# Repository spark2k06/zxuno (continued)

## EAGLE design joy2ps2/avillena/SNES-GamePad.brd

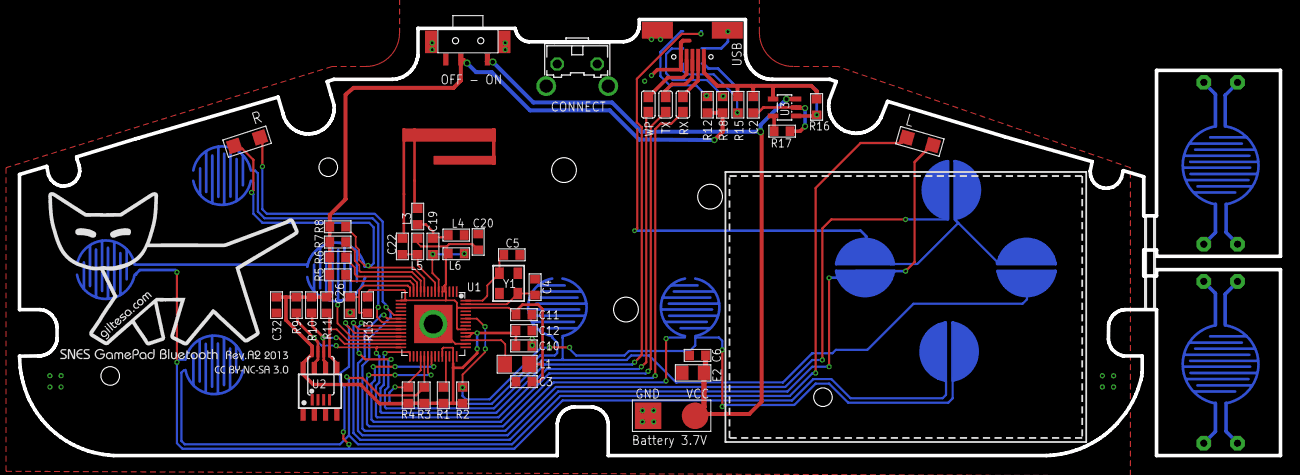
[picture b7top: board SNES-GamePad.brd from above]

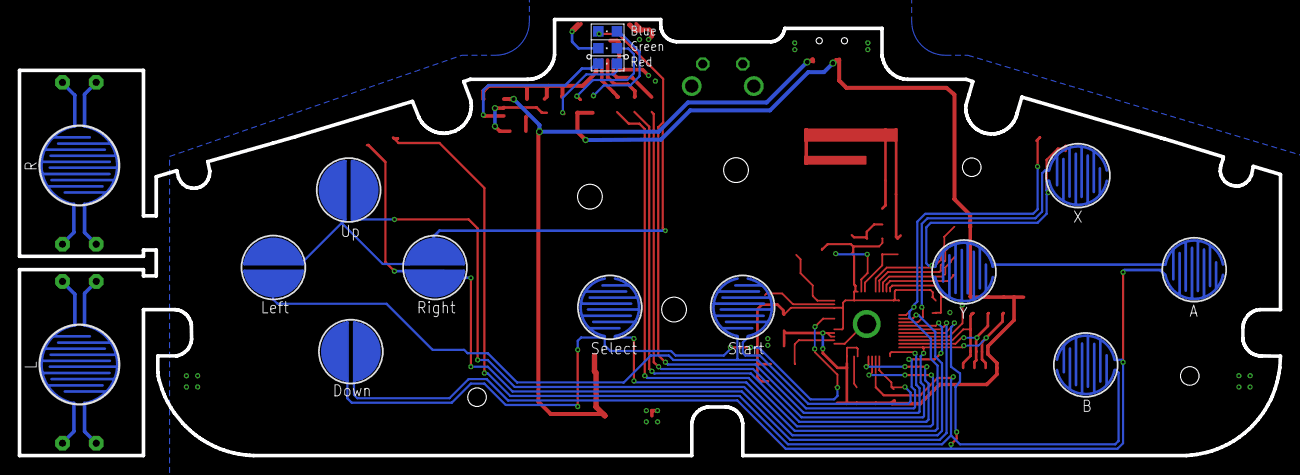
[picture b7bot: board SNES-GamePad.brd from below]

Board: 2 copper layers, 142.4 x 49.3 mm, 67 parts (15 on the bottom side), 43 nets.

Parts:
A1: ANTENA; ANTENA-AIROHA
BATTERY: VCC 3.7V; 1X02_SMD_BIG
BTN-0: L; 1X02_SMD
BTN-0': L; SNES_GAMEPAD_RL
BTN-1: R; 1X02_SMD
BTN-1': R; SNES_GAMEPAD_RL
BTN-2: UP; BUTTON-CONDUCTIVE-PAD
BTN-3: X; BUTTON-CONDUCTIVE-BUTTON
BTN-4: LEFT; BUTTON-CONDUCTIVE-PAD
BTN-5: RIGHT; BUTTON-CONDUCTIVE-PAD
BTN-6: A; BUTTON-CONDUCTIVE-BUTTON
BTN-7: Y; BUTTON-CONDUCTIVE-BUTTON
BTN-8: DOWN; BUTTON-CONDUCTIVE-PAD
BTN-9: B; BUTTON-CONDUCTIVE-BUTTON
BTN-DEL: SLECT; BUTTON-CONDUCTIVE-BUTTON
BTN-ENTER: START; BUTTON-CONDUCTIVE-BUTTON
BTN-RST: CONNECT; SWITCH-90º
C2, C3, C4, C5, C6, C10, C11, C12, C19, C20, C22, C26, C32: C0603
E2: C0805
L1: C1206
L3, L4, L5, L6: C0603
LBLUE: CHIPLED_0805
LGREEN: CHIPLED_0805
LRED: CHIPLED_0805
R1, R2, R3, R4, R5, R6, R7, R8: 22kΩ; R0603
R9, R17: 4.7kΩ; R0603
R10, R11: 2.2kΩ; R0603
R12, R15: 330Ω; R0603
R13: 10Ω; R0603
R16: 10kΩ; R0603
R18: 1kΩ; R0603
S2: INTERRUPTOR_1
SJ1, SJ2, SJ3: JUMPER-SMD
U1: AIROHA AB1108; QFN56_6MM
U2: EEPROM1; TSSOP8
U2': EEPROM2; M8-EEPROM
U3: SOT23-5
U$1: SNES-LOGO
USB: MICRO_USB_1
Y1: CRISTAL; CRISTAL-SMD-3X2.5MM

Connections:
3.7V: BATTERY.VCC, C6.1, E2.1, S2.VCCIN, U3.1
5V: C2.1, R15.2, R16.2, U3.5, USB.VCC
BAT: C10.1, C12.1, C32.2, R1.1, R2.1, R3.1, R4.1, R5.2, R6.2, R7.2, R8.2, R9.1, R10.1, R11.1, R12.1, R18.2, S2.VCCOUT, U1.P10, U1.P11, U1.P16, U1.P19, U2.8, U2'.8
COL1: BTN-1.1, BTN-DEL.2, U1.P38
COL2: BTN-2.2, U1.P37
COL3: BTN-3.1, U1.P36
COL4: BTN-4.1, BTN-ENTER.1, U1.P35
COL5: BTN-0.1, BTN-5.2, U1.P34
COL6: BTN-6.2, BTN-8.2, BTN-9.2, U1.P33
COL7: BTN-7.2, U1.P32
CONNECT: BTN-RST.1, U1.P48
FIL1: BTN-1.2, BTN-2.1, BTN-3.2, BTN-4.2, BTN-5.1, BTN-6.1, BTN-7.1, R8.1, U1.P47
FIL2: BTN-8.1, BTN-DEL.1, R2.2, U1.P6
FIL3: BTN-0.2, BTN-9.1, R3.2, U1.P24
FIL4: BTN-ENTER.2, R4.2, U1.P25
GND: A1.GND, BATTERY.GND, BTN-RST.2, BTN-RST.GND1, BTN-RST.GND2, C2.2, C3.2, C4.1, C5.1, C6.2, C10.2, C11.1, C12.2, C20.1, C22.1, C26.2, C32.1, E2.2, L4.1, LGREEN.C, R17.2, S2.GND1, S2.GND2, U1.P0, U1.P13, U2.1, U2.2, U2.3, U2.4, U2'.1, U2'.2, U2'.3, U2'.4, U3.2, USB.GND0, USB.GND1, USB.GND2, Y1.GND1, Y1.GND2
unnamed: LRED.A, R15.1
unnamed: C22.2, L5.2, U1.P50
unnamed: SJ1.2, USB.OTG
unnamed: LGREEN.A, R18.1
unnamed: C19.1, L3.2, L4.2
unnamed: A1.SIGNAL, L3.1
unnamed: C19.2, L6.2, U1.P51
unnamed: SJ3.2, USB.D-
unnamed: SJ2.2, USB.D+
unnamed: LBLUE.C, U1.P28
unnamed: LRED.C, R16.1, U3.3
unnamed: R17.1, U3.4
unnamed: LBLUE.A, R12.2
unnamed: C26.1, R13.1, U1.P43
unnamed: C3.1, C11.2, C20.2, L1.2, L5.1, L6.1, R13.2, U1.P3, U1.P9, U1.P42, U1.P52, U1.P53
unnamed: R1.2, U1.P18
unnamed: R5.1, U1.P44
unnamed: R6.1, U1.P45
unnamed: R7.1, U1.P46
unnamed: L1.1, U1.P12
RX: SJ3.1, U1.P23
SCL: R10.2, U1.P30, U2.6, U2'.6
SDA: R11.2, U1.P31, U2.5, U2'.5
TX: SJ2.1, U1.P22
WP: R9.2, SJ1.1, U1.P29, U2.7, U2'.7
X1: C5.2, U1.P1, Y1.P2
X2: C4.2, U1.P2, Y1.P1

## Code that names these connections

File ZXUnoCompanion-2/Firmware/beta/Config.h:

// Fichero de configuracion del firmware de Sugarless +2

#define membrane13x11 // Desactivado para membranas de 5x8 si se quiere ahorrar tiempo de proceso del avr

#define atmega2560 // Activado para Arduino Mega
//#define atmega128 // Activado para Atmega128

#define PA 1 //
#define PB 2 //
#define PC 3 //
#define PD 4 //
#define PE 5 //
#define PG 7 //
#define PH 8 //
#define PL 12 //

#define ROWS8 8		//Numero de Filas de teclado 8x5
#define COLS5 5		//Numero de Columnas de teclado 8x5

#define ROWS 13		//Numero de Filas de teclado 13x11
#define COLS 11		//Numero de Columnas de teclado 13x11

//#define xchg_del_break // Solo aplicable a teclados +2A/+3
//#define cursors_kbpc // Solo aplicable a teclados +2A/+3
// Mapa de la matriz
// 1x1 = '1', 1x2 = '2'
// 2x1 = 'Q', 2x2 = 'W'
// ...

#ifdef atmega128

#define LED_ON				PORTA |= (1<<4)   
#define LED_OFF				PORTA &= ~(1<<4)
#define LED_CONFIG			DDRA |= (1<<4)

#define KBEXT_BIDIR_ON		PORTF |= (1<<1)   
#define KBEXT_BIDIR_OFF		PORTF &= ~(1<<1)
#define KBEXT_BIDIR_CONFIG	DDRF |= (1<<1)

#define POWER_ON			PORTA |= (1<<7)   
#define POWER_OFF			PORTA &= ~(1<<7)
#define POWER_CONFIG		DDRA |= (1<<7)

#define RESET_ON			DDRA |= (1<<5); PORTA &= ~(1<<5) // GND
#define RESET_OFF			DDRA &= ~(1<<5); PORTA |= (1<<5) // HI-Z

#define SYSTEM_PIN			6
#define SYSTEM_BCD			PA

#define PS2_DAT				PF3
#define PS2_CLK				PF2

#define PS2_PORT			PORTF
#define PS2_DDR				DDRF
#define PS2_PIN				PINF

//{PC3, PC1, PG1, PD7, PD5, PD3, PD1, PG4, PB7, PB5, PB3};
uint8_t pinsC[COLS] = { 3,  1,  1,  7,  5,  3,  1,  4,  7,  5,  3 };
uint8_t bcdC[COLS] = { PC, PC, PG, PD, PD, PD, PD, PG, PB, PB, PB };

//{PB4, PB6, PG3, PD0, PD2, PD4, PD6, PG0, PC0, PC2, PC4, PC6, PC7};
uint8_t pinsR[ROWS] = { 4,  6,  3,  0,  2,  4,  6,  0,  0,  2,  4,  6,  7 };
uint8_t bcdR[ROWS] = { PB, PB, PG, PD, PD, PD, PD, PG, PC, PC, PC, PC, PC };

//{PE5(1), PE4(2), PE3(3), PE2(4), PE1(6), PE0(7), PC5(9)};
uint8_t pinsJOY2PS2[7] = { 5, 4, 3, 2, 1, 0, 9 };
uint8_t bcdJOY2PS2[7] = { PE, PE, PE, PE, PE, PC};

uint8_t TZX_ROOT_PIN = 2, TZX_ROOT_BCD = PB;
uint8_t TZX_UP_PIN = 1, TZX_UP_BCD = PB;
uint8_t TZX_DOWN_PIN = 0, TZX_DOWN_BCD = PB;
uint8_t TZX_PLAY_PIN = 7, TZX_PLAY_BCD = PE;
uint8_t TZX_STOP_PIN = 6, TZX_STOP_BCD = PE;

#endif

#ifdef atmega2560

#define LED_ON				PORTL |= (1<<0)   
#define LED_OFF				PORTL &= ~(1<<0)
#define LED_CONFIG			DDRB |= (1<<7)

#define KBEXT_BIDIR_ON      PORTB |= (1<<3)   
#define KBEXT_BIDIR_OFF     PORTB &= ~(1<<3)
#define KBEXT_BIDIR_CONFIG  DDRB |= (1<<3)

#define POWER_ON			PORTB |= (1<<2)   
#define POWER_OFF			PORTB &= ~(1<<2)
#define POWER_CONFIG		DDRB |= (1<<2)

#define RESET_ON			DDRB |= (1<<0); PORTB &= ~(1<<0) // GND
#define RESET_OFF			DDRB &= ~(1<<0); PORTB |= (1<<0) // HI-Z

#define SYSTEM_PIN			1
#define SYSTEM_BCD			PB

#define PS2_DAT				PF3
#define PS2_CLK				PF2

#define PS2_PORT			PORTF
#define PS2_DDR				DDRF
#define PS2_PIN				PINF

//{PL7, PG1, PD7, PC1, PC3, PC5, PC7, PA6, PA4, PA2, PA0};
uint8_t pinsC[COLS] = { 7,  1,  7,  1,  3,  5,  7,  6,  4,  2,  0 };
uint8_t bcdC[COLS] = { PL, PG, PD, PC, PC, PC, PC, PA, PA, PA, PA };

//{PA1, PA3, PA5, PA7, PC6, PC4, PC2, PC0, PG2, PG0, PL6, PL4, PL2};
uint8_t pinsR[ROWS] = { 1,  3,  5,  7,  6,  4,  2,  0,  2,  0,  6,  4,  2 };
uint8_t bcdR[ROWS] = { PA, PA, PA, PA, PC, PC, PC, PC, PG, PG, PL, PL, PL };

//{PH4(1), PH5(2), PH6(3), PB4(4), PB5(6), PB6(7), PL5(9)};
uint8_t pinsJOY2PS2[7] = { 4, 5, 6, 4, 5, 6, 5 };
uint8_t bcdJOY2PS2[7] = { PH, PH, PH, PB, PB, PB, PL };

uint8_t TZX_ROOT_PIN = 4, TZX_ROOT_BCD = PE;
uint8_t TZX_UP_PIN = 5, TZX_UP_BCD = PE;
uint8_t TZX_DOWN_PIN = 5, TZX_DOWN_BCD = PG;
uint8_t TZX_PLAY_PIN = 3, TZX_PLAY_BCD = PE;
uint8_t TZX_STOP_PIN = 3, TZX_STOP_BCD = PH;

#endif

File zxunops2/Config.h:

// Fichero de configuracion

//#define switches // Activado para el ZXGo+
//#define atmega644 // Activado para teclado +2A/+3 con atmega644

#define PA 1 //
#define PB 2 //
#define PC 3 //
#define PD 4 //

#define ROWS8 8		//Numero de Filas de teclado 8x5
#define COLS5 5		//Numero de Columnas de teclado 8x5

// Mapa de la matriz
// 1x1 = '1', 1x2 = '2'
// 2x1 = 'Q', 2x2 = 'W'
// ...

#ifdef atmega644

#define ROWS 13		//Numero de Filas de teclado en atmega 644
#define COLS 11		//Numero de Columnas de teclado en atmega 644

#define PS2_DAT		PA7
#define PS2_CLK		PA6

#define PS2_PORT	PORTA
#define PS2_DDR		DDRA
#define PS2_PIN		PINA

//{PA4, PA3, PA2, PA1, PA0, PB0, PB1, PB2, PB3, PB4, PB5};
uint8_t pinsC[COLS] = { 4,  3,  2,  1,  0,  0,  1,  2,  3,  4,  5 };
uint8_t bcdC[COLS] = { PA, PA, PA, PA, PA, PB, PB, PB, PB, PB, PB };

//{PC7, PC6, PC5, PC4, PC3, PC2, PC1, PC0, PD4, PD3, PD2, PD1, PD0};
uint8_t pinsR[ROWS] = { 7,  6,  5,  4,  3,  2,  1,  0,  4,  3,  2,  1,  0 };
uint8_t bcdR[ROWS] = { PC, PC, PC, PC, PC, PC, PC, PC, PD, PD, PD, PD, PD };

#else

#define ROWS 8		//Numero de Filas de teclado en atmega 168/328
#define COLS 5		//Numero de Columnas de teclado en atmega 168/328

#define PS2_DAT		PC4
#define PS2_CLK		PC5

////////Pro Mini
#define PS2_PORT	PORTC
#define PS2_DDR		DDRC
#define PS2_PIN		PINC

#define LED_ON	PORTB |= (1<<5)		
#define LED_OFF	PORTB &= ~(1<<5)
#define LED_CONFIG	DDRB |= (1<<5) //Led en PB5 en Pro mini y similares

//{PC1, PC0, PB4, PB3, PB2};
uint8_t pinsC[COLS] = {  1,  0,  4,  3,  2 }; // Configuracion de pines en el ZXGo+
uint8_t bcdC[COLS] =  { PC, PC, PB, PB, PB }; // Configuracion de pines en el ZXGo+

//{PD2, PD3, PD4, PD5, PD6, PD7, PB0, PB1};
uint8_t pinsR[ROWS] = {  2,  3,  4,  5,  6,  7,  0,  1 }; // Configuracion de pines en el ZXGo+
uint8_t bcdR[ROWS] =  { PD, PD, PD, PD, PD, PD, PB, PB }; // Configuracion de pines en el ZXGo+

#endif

#ifdef switches
//Swiches {PC2=A2 / PC3=A3}; 
#define NUMSW 2 //Numero de botones externos en Arduino
uint8_t pinsSW[NUMSW] = { 2, 3 };
uint8_t bcdSW[NUMSW] = { 3, 3 };
#endif

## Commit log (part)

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2018-02-24 Issue 1
2018-03-02 Release 7
2018-03-02 Alpha 1
2018-03-10 Alpha 2
2018-03-14 Alpha 3
2018-03-21 Alpha 4
2018-03-28 Beta 1
2018-04-03 Beta 2
2018-04-09 Beta 3
2018-04-10 Beta 4
2018-04-12 Infografia por yoxxxoy
    Infografía de la configuracion de Jumpers por yoxxxoy.
2018-04-12 Infografía por yoxxxoy.
    Infografía de la configuracion de Jumpers por yoxxxoy.
2018-04-12 Infografía por yoxxxoy
    Infografía de la configuracion de Jumpers por yoxxxoy
2018-05-02 Beta 5
2018-05-09 Release 1
2018-05-09 Release 7.1
2018-05-14 Release 1.1
2018-10-08 Release 7.1.1
    Le faltaba un } al último else de la función de setup(), gracias iturbez del foro de zxuno por el aviso.
2018-11-21 Limpieza de repositorio
2018-11-21 Reorganizacion de repositorio
2019-01-12 Release 2
2019-04-20 Release 8
2021-05-19 1.1
    Deteccion correcta la SRAM de 1024KB
2021-05-23 Opción de monocromo (Verde, ámbar y B&W)
2021-05-31 Cambio de paleta monocromática
    Se cambia la paleta de tonalidades monocromáticas para representar mejor los colores brillantes, gracias @desUBIKado por la sugerencia.
2021-06-06 Version alternativa para memoria SRAM externa
    Para sintetizar, adicionalmente se debe deshabilitar los modulos WiFi y MIDI desde el fichero de configuracion common/config.vh
2021-06-08 SAA1099, Control WiFi y Turbo
    Se añade SAA1099, gracias a azesmbog
    Se controla el encendido y apagado de WiFi con F11
    La activación y desactivación del modo Turbo (28 Mhz) con F12 ahora se produce al soltar la tecla, y se mantiene el estado
2021-06-09 SAA1099 y PZX, sin WiFi ni MIDI para SRAM interna
2021-06-09 Opcion de monocromo como modulo opcional
2021-06-13 PZX Loader: Añadir funcionalidad de marca de usuario y rebobinado a esa marca (Contador a 0)
2021-06-13 Cambiado a CTRL-F8 para rewind de fichero y restaurado F9 para STOP
2021-06-13 Actualización de binarios
2021-06-13 Añado la licencia correspondiente
2021-06-21 Version para ZXUncore
    Uso de RGB666 para mejora de la opción monocromática. Ahora se visualiza correctamente incluso en modos de ULA+
2021-08-11 Compatibilidad joysplitter
    Compatibilidad con el puerto 1 del joysplitter de antoniovillena
2021-08-31 ON/OFF WiFi Reset opcional
2021-09-02 Fix to lack of sound in some games, by @vanfanel
2021-09-08 Merge with version "multi" of ZXUno SVN repository
    Merge with the latest version of the ZXUno SVN repository, which has settings with different settings:
    * Simple Joystick
    * Double Joystick (Jamma or Version 2M by ManuFerHi)
    * JoySplitter by Antonio Villena
2021-10-07 Joystick splitter support
2021-10-08 Correccion a #3: Si el splitter está desactivado o no esta presente por la compilacion condicional, la linea fire3 se deja a 1 para solventar problemas con mandos de megadrive.
2021-11-14 PZX hasta 216KB con SRAM de 512KB
    Cuando el core se usa con 512KB de SRAM, la carga del PZX se lleva a cabo mediante los bancos 13,14,15,22,23,24,25,26,27,28,29,30,31 y 8Kb del banco 12, lo que nos ofrece un total de 216KB.
2022-02-02 Cambios JoySplitter y MonochromeRGB en ZXUnCore
    * Uso del bit 5 del DEVCTRL2 para el JoySplitter
    * Mejora del modulo de MonochromeRGB en la version ZXUnCore, gracias a Fernando Mosquera (@benitoss)
2022-02-02 Fix binarios SPECTRUM.ZX1
    Actualización de los binarios de Spectrum, los había subido con más tamaño del debido.
2022-02-03 Soporte del segundo disparo en JoyKB
    Se añade soporte del segundo botón de disparo en el Joystick de teclado:
    KEYPAD 0 o cualquiera de las teclas de Menú de Windows.
2022-02-04 Correcciones y mejoras
    * Correcciones del Splitter DB9
    * Soporte para segundo puerto de Joystick
2022-02-05 Rollback del modulo SPI a la version de Julio2020
    Identificado el problema de error cargando CPM, se procede a realizar un rollback. Si se encuentra la causa del fallo en el modulo, se volverá a actualizar corrigiendolo.
2022-02-08 Reset de teclado al inicio del core
    Se estable un reset de teclado para forzar el establecimiento del SET 2, solo al inicio del core, no en un reset, master-reset, hard-reset, etc...
    Esta característica es útil para no tener que desconectar el ZXUno después del uso del core de PCXT, el cual establece el SET 1 de ScanCodes. De esta forma, será posible volver al core de Spectrum me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
    Las versiones de memoria externa y vga2m no se actualizan, debido a que no cabe manteniendo sus características de lector de PZX y sonido SAA, que son más importantes. No obstante, cualquiera puede r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
2022-02-24 Frame timing is slightly out of sync with the NES frame by 2 clocks here we take back 1 clock each from line 480 and 500, which are off screen and corrects the slight error. Also position of backporc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
2022-02-24 Removed commented out code
2022-02-25 Actualizacion de binarios
    * Bug fix VGA (by @ZXMicroJack)
    * Unificación de binarios. Ahora se mantiene una única versión para memoria interna, compatible con los modelos de 512Kb y 2Mb.
2022-04-04 Inidicador de actividad WiFi (OSD)
2022-08-04 Added Covox Soundrive support Added Timex joystick support Added Timex AY ports support
2022-08-05 Actualizacion de binarios
2022-08-05 Fix border chane when writting AY registers
2022-08-05 Actualizacion de binarios y configuracion de VGA2M
2022-08-06 Correccion de video cuando no esta activo WiFi OSD
2022-08-21 Nuevo proyecto vgawifi
2022-09-24 root mode removed
2022-09-24 fixing tildes
2022-09-25 Update binaries
2024-06-19 Small Revision
    Small Revision
